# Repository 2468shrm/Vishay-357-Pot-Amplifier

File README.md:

# Vishay-357-Pot-Amplifier

A unity-gain amplifier circut for the Vishay 357 series potentiometers. It mounts
on the back of the pot.

J1 Configures the voltage across the potentiometer, it allows for forward and
reverse adaption.
- Forward:  1-3 and 4-6
- Reverse:  3-5 and 2-4

J2 uses a socket header (female) to allow use of purchased FRC PWM cable to
connect between sensor and roboRIO.

J2 also provides power to the sensor. The circuit works with a VDD of 3.3V
to 5V, so this works with roboRIO as well as Feather and 3.3V MCU solutions.

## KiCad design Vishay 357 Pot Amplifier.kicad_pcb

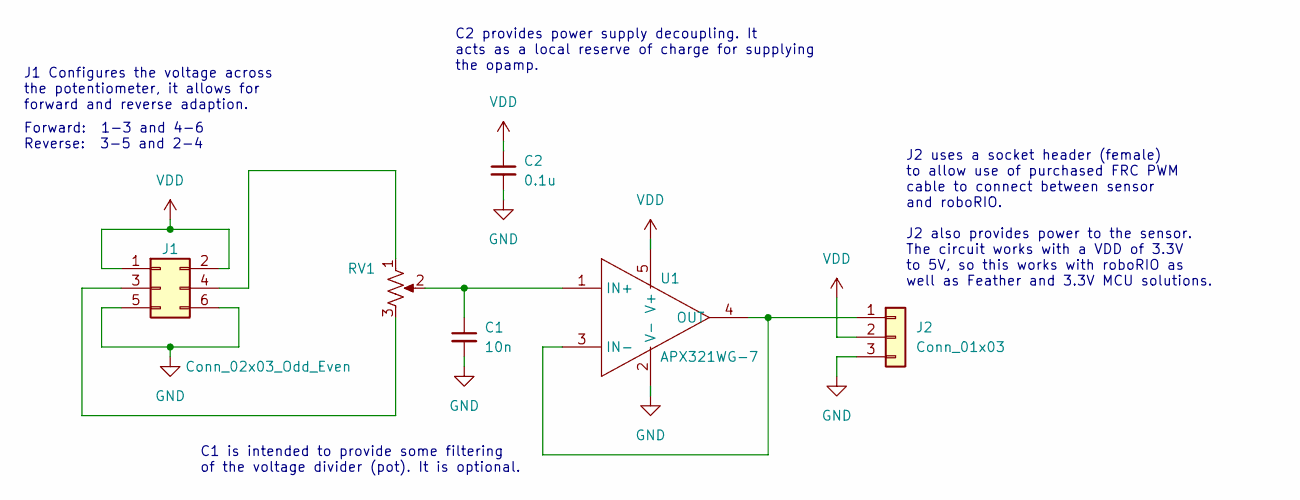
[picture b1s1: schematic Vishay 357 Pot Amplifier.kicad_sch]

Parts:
C1: 10n; C_1206_3216Metric
C2: 0.1u; C_1206_3216Metric
J1: Conn_02x03_Odd_Even; PinHeader_2x03_P2.54mm_Vertical
J2: Conn_01x03; PinHeader_1x03_P2.54mm_Vertical
RV1: R_Potentiometer_US; Vishay_357
U1: APX321WG-7; SOT95P285X145-5N; Manufacturer_Part_Number APX321WG-7; Mouser Part Number 621-APX321WG-7

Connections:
GND: C1.2, C2.2, J1.5, J1.6, J2.3, U1.2 (V-)
unnamed: C1.1, RV1.2, U1.1 (IN+)
unnamed: J1.4, RV1.1
unnamed: J2.1, U1.3 (IN-), U1.4 (OUT)
unnamed: J1.3, RV1.3
VDD: C2.1, J1.1, J1.2, J2.2, U1.5 (V+)

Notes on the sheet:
C2 provides power supply decoupling. It acts as a local reserve of charge for supplying the opamp.
C1 is intended to provide some filtering of the voltage divider (pot). It is optional.
Forward: 1-3 and 4-6 Reverse: 3-5 and 2-4
J2 also provides power to the sensor. The circuit works with a VDD of 3.3V to 5V, so this works with roboRIO as well as Feather and 3.3V MCU solutions.
J2 uses a socket header (female) to allow use of purchased FRC PWM cable to connect between sensor and roboRIO.
J1 Configures the voltage across the potentiometer, it allows for forward and reverse adaption.

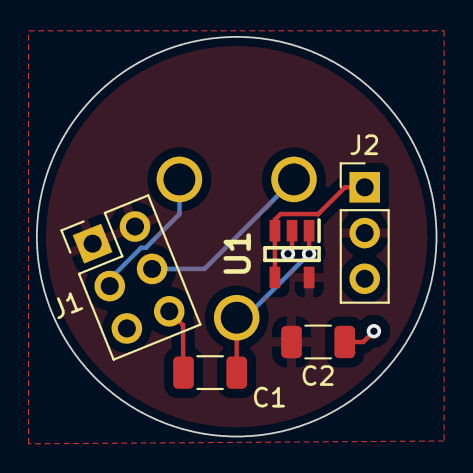
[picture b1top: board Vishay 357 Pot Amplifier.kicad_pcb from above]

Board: 2 copper layers, 22.2 x 22.2 mm, 6 parts (1 on the bottom side), 6 nets.

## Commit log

2024-01-05 adding KiCAD files
2024-01-05 adding images for docs
2024-01-05 added manufacturing files (Gerbers)
2024-01-05 updated readme to include design info and images

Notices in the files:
Vishay 357 Pot Amplifier.kicad_pcb:
(c) 2023 SHRM
